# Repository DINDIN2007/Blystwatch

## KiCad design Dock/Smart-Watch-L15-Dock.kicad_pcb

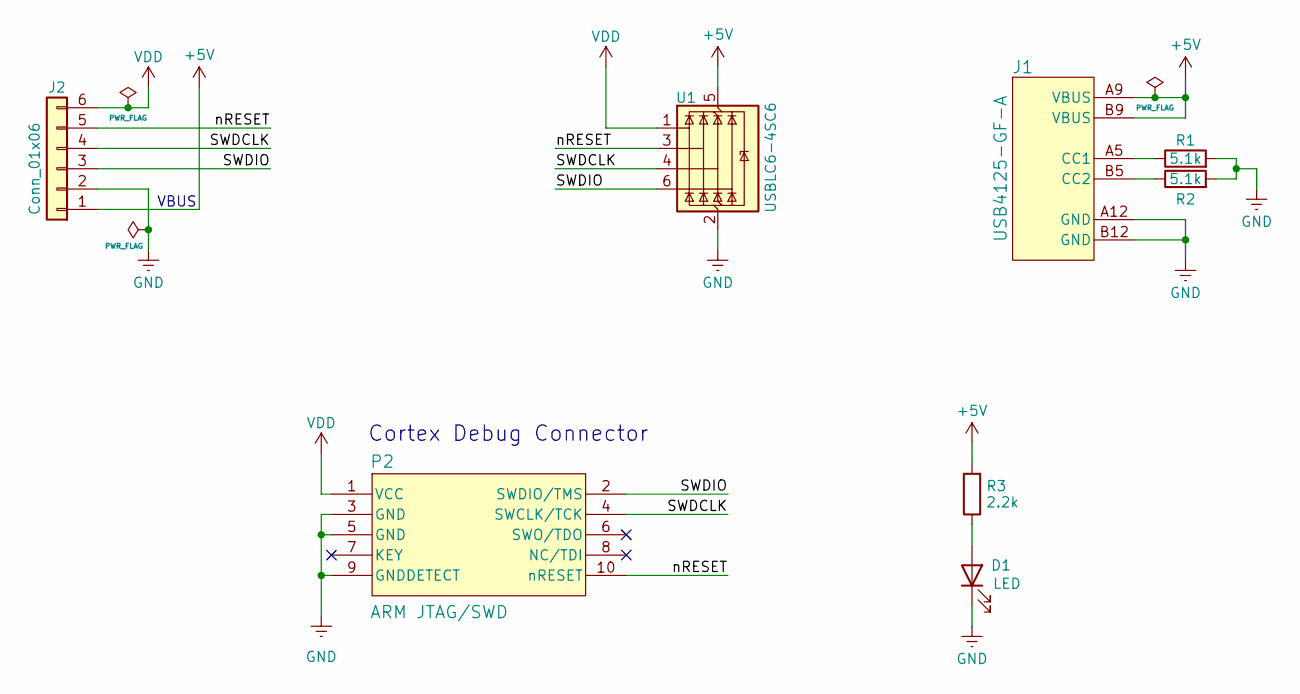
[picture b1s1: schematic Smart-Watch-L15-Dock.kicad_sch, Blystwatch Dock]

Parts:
D1: LED; LED_0603_1608Metric_Pad1.05x0.95mm_HandSolder
J1: USB4125-GF-A; CONN6_USB4125_GCT
J2: Conn_01x06; PinHeader_1x06_P2.54mm_Vertical
P2: ARM JTAG/SWD; CON10_2X5_DUK_FTSH_SAI-M
R1, R2: 5.1k; R_0805_2012Metric_Pad1.20x1.40mm_HandSolder
R3: 2.2k; R_0805_2012Metric_Pad1.20x1.40mm_HandSolder
U1: USBLC6-4SC6; SOT-23-6

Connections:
+5V: J1.A9 (VBUS), J1.B9 (VBUS), J2.1, R3.2, U1.5 (VBUS)
/SWDCLK: J2.4, P2.4 (SWCLK/TCK), U1.4 (I/O3)
/SWDIO: J2.3, P2.2 (SWDIO/TMS), U1.6 (I/O4)
/nRESET: J2.5, P2.10 (nRESET), U1.3 (I/O2)
GND: D1.1 (K), J1.A12 (GND), J1.B12 (GND), J2.2, P2.3 (GND), P2.5 (GND), P2.9 (GNDDETECT), R1.2, R2.2, U1.2 (GND)
unnamed: D1.2 (A), R3.1
unnamed: J1.A5 (CC1), R1.1
unnamed: J1.B5 (CC2), R2.1
VDD: J2.6, P2.1 (VCC), U1.1 (I/O1)

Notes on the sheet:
VBUS
Cortex Debug Connector

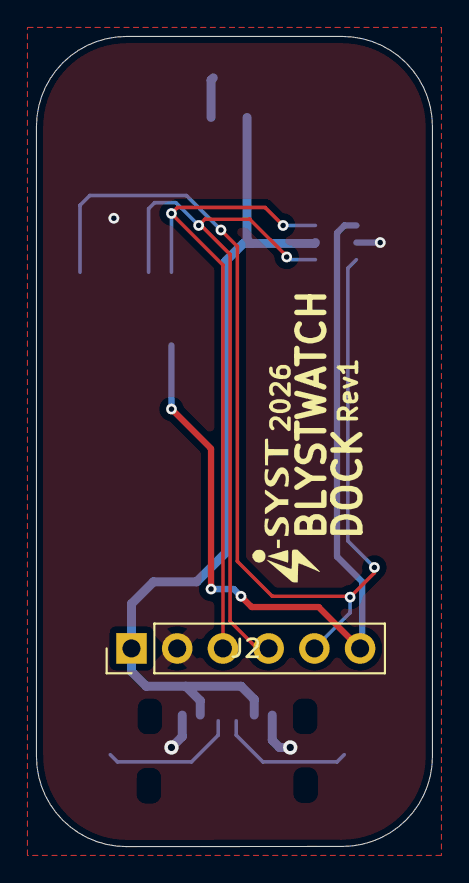
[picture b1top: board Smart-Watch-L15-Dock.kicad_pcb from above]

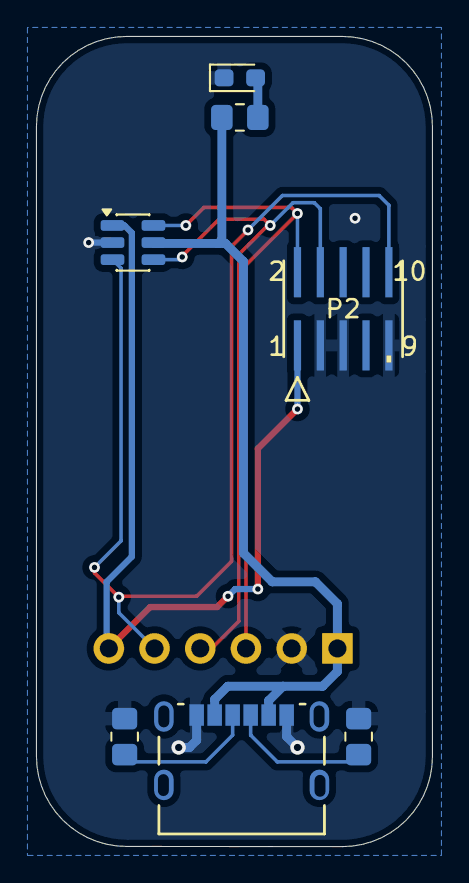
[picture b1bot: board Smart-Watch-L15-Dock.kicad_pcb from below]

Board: 2 copper layers, 22.0 x 45.0 mm, 8 parts (7 on the bottom side), 9 nets.

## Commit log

2026-05-12 Watch Finalization and PCB Draft for the Dock
2026-05-12 Screenshots
2026-05-12 Enhance README with hardware design details
    Expanded the README to include detailed hardware design information, core components, and constraints for the Smart-Watch-L15 project.
2026-05-12 Fix image links for 3D renders in README
    Updated image references for the 3D renders in README.
